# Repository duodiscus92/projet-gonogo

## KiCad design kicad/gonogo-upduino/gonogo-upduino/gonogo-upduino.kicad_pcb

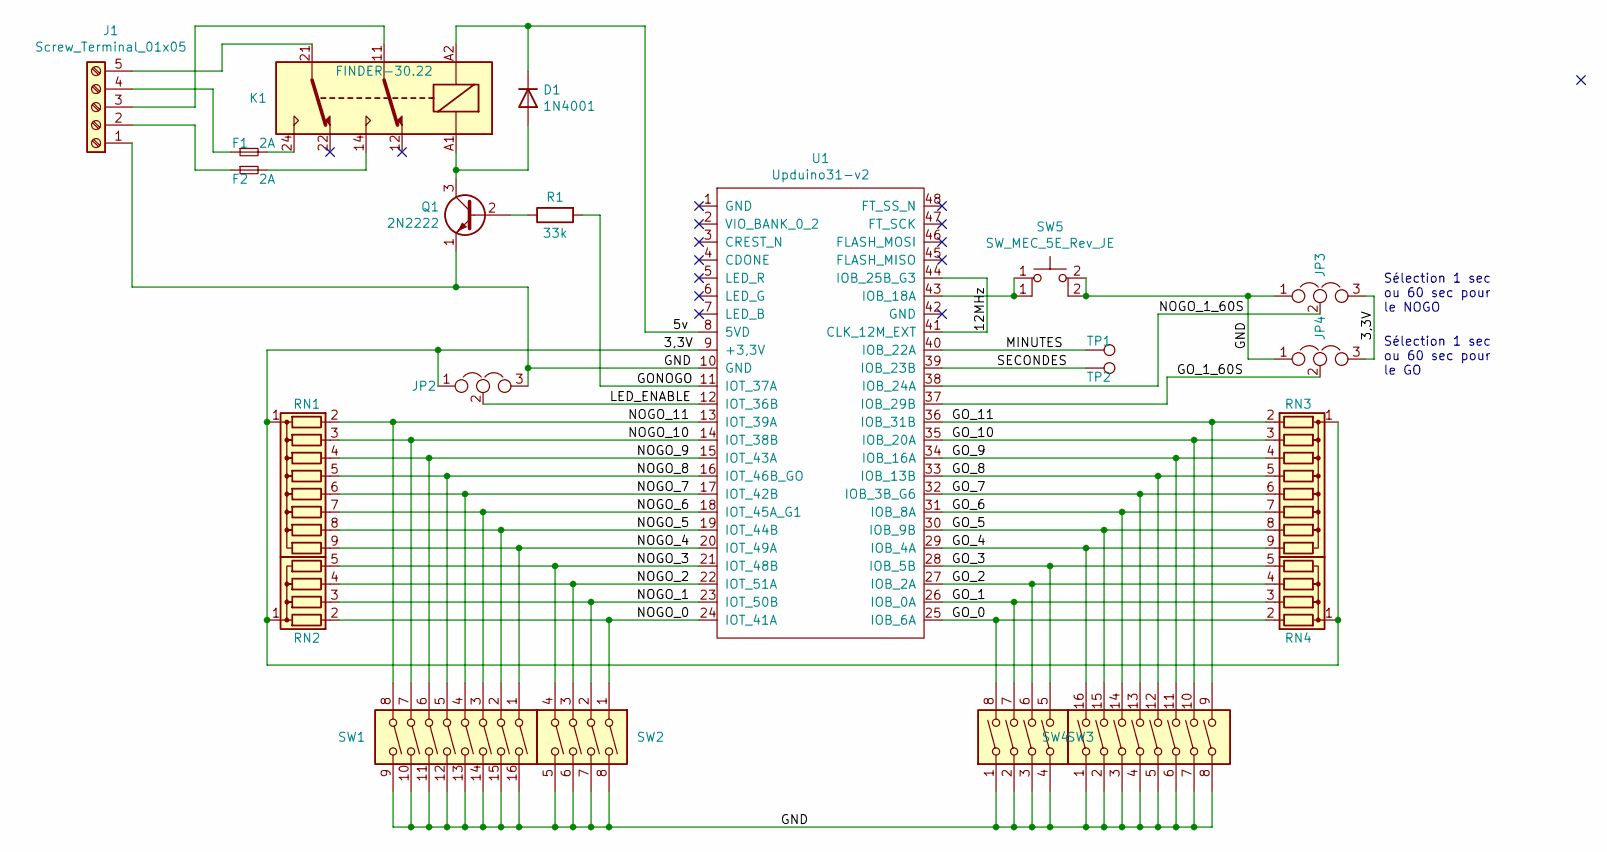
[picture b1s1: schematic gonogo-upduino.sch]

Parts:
D1: 1N4001; D_DO-41_SOD81_P10.16mm_Horizontal
F1, F2: 2A; Fuseholder_TR5_Littelfuse_No560_No460
J1: Screw_Terminal_01x05; TerminalBlock_bornier-5_P5.08mm
JP2, JP3, JP4: Jumper_NC_Dual; PinHeader_1x03_P2.54mm_Vertical
K1: FINDER-30.22; Relay_DPDT_Finder_30.22
Q1: 2N2222; TO-18-3
R1: 33k; R_Axial_DIN0207_L6.3mm_D2.5mm_P2.54mm_Vertical
RN1, RN3: R_Network08; R_Array_SIP9
RN2, RN4: R_Network04; R_Array_SIP5
SW1, SW4: SW_DIP_x08; DIP-16_W7.62mm_Socket
SW2, SW3: SW_DIP_x04; DIP-8_W7.62mm_Socket
SW5: SW_MEC_5E_Rev_JE; SW_PUSH_6mm
TP1, TP2: TestPoint; TestPoint_THTPad_3.0x3.0mm_Drill1.5mm
U1: Upduino31-v2; DIP-48_W17.78mm_LongPads

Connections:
/3,3V: JP2.1, JP3.3, JP4.3, RN1.1 (common), RN2.1 (common), RN3.1 (common), RN4.1 (common), U1.9 (+3,3V)
/5v: D1.1 (K), K1.A2, U1.8 (5VD)
/12MHz: U1.41 (CLK_12M_EXT), U1.44 (IOB_25B_G3)
/GND: J1.1, JP2.3, JP3.1, JP4.1, Q1.1 (E), SW1.9, SW1.10, SW1.11, SW1.12, SW1.13, SW1.14, SW1.15, SW1.16, SW2.5, SW2.6, SW2.7, SW2.8, SW3.1, SW3.2, SW3.3, SW3.4, SW4.1, SW4.2, SW4.3, SW4.4, SW4.5, SW4.6, SW4.7, SW4.8, SW5.2 (A), U1.10 (GND)
/GONOGO: R1.2, U1.11 (IOT_37A)
/GO_0: RN4.2 (R1), SW3.8, U1.25 (IOB_6A)
/GO_1: RN4.3 (R2), SW3.7, U1.26 (IOB_0A)
/GO_1_60S: JP4.2, U1.37 (IOB_29B)
/GO_2: RN4.4 (R3), SW3.6, U1.27 (IOB_2A)
/GO_3: RN4.5 (R4), SW3.5, U1.28 (IOB_5B)
/GO_4: RN3.9 (R8), SW4.16, U1.29 (IOB_4A)
/GO_5: RN3.8 (R7), SW4.15, U1.30 (IOB_9B)
/GO_6: RN3.7 (R6), SW4.14, U1.31 (IOB_8A)
/GO_7: RN3.6 (R5), SW4.13, U1.32 (IOB_3B_G6)
/GO_8: RN3.5 (R4), SW4.12, U1.33 (IOB_13B)
/GO_9: RN3.4 (R3), SW4.11, U1.34 (IOB_16A)
/GO_10: RN3.3 (R2), SW4.10, U1.35 (IOB_20A)
/GO_11: RN3.2 (R1), SW4.9, U1.36 (IOB_31B)
/LED_ENABLE: JP2.2, U1.12 (IOT_36B)
/MINUTES: TP1.1, U1.40 (IOB_22A)
/NOGO_0: RN2.2 (R1), SW2.1, U1.24 (IOT_41A)
/NOGO_1: RN2.3 (R2), SW2.2, U1.23 (IOT_50B)
/NOGO_1_60S: JP3.2, U1.38 (IOB_24A)
/NOGO_2: RN2.4 (R3), SW2.3, U1.22 (IOT_51A)
/NOGO_3: RN2.5 (R4), SW2.4, U1.21 (IOT_48B)
/NOGO_4: RN1.9 (R8), SW1.1, U1.20 (IOT_49A)
/NOGO_5: RN1.8 (R7), SW1.2, U1.19 (IOT_44B)
/NOGO_6: RN1.7 (R6), SW1.3, U1.18 (IOT_45A_G1)
/NOGO_7: RN1.6 (R5), SW1.4, U1.17 (IOT_42B)
/NOGO_8: RN1.5 (R4), SW1.5, U1.16 (IOT_46B_GO)
/NOGO_9: RN1.4 (R3), SW1.6, U1.15 (IOT_43A)
/NOGO_10: RN1.3 (R2), SW1.7, U1.14 (IOT_38B)
/NOGO_11: RN1.2 (R1), SW1.8, U1.13 (IOT_39A)
/SECONDES: TP2.1, U1.39 (IOB_23B)
unnamed: D1.2 (A), K1.A1, Q1.3 (C)
unnamed: F1.1, J1.4
unnamed: F1.2, K1.24
unnamed: F2.1, J1.2
unnamed: F2.2, K1.14
unnamed: J1.3, K1.11
unnamed: J1.5, K1.21
unnamed: Q1.2 (B), R1.1
unnamed: SW5.1, U1.43 (IOB_18A)

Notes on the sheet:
Sélection 1 sec ou 60 sec pour le NOGO
Sélection 1 sec ou 60 sec pour le GO

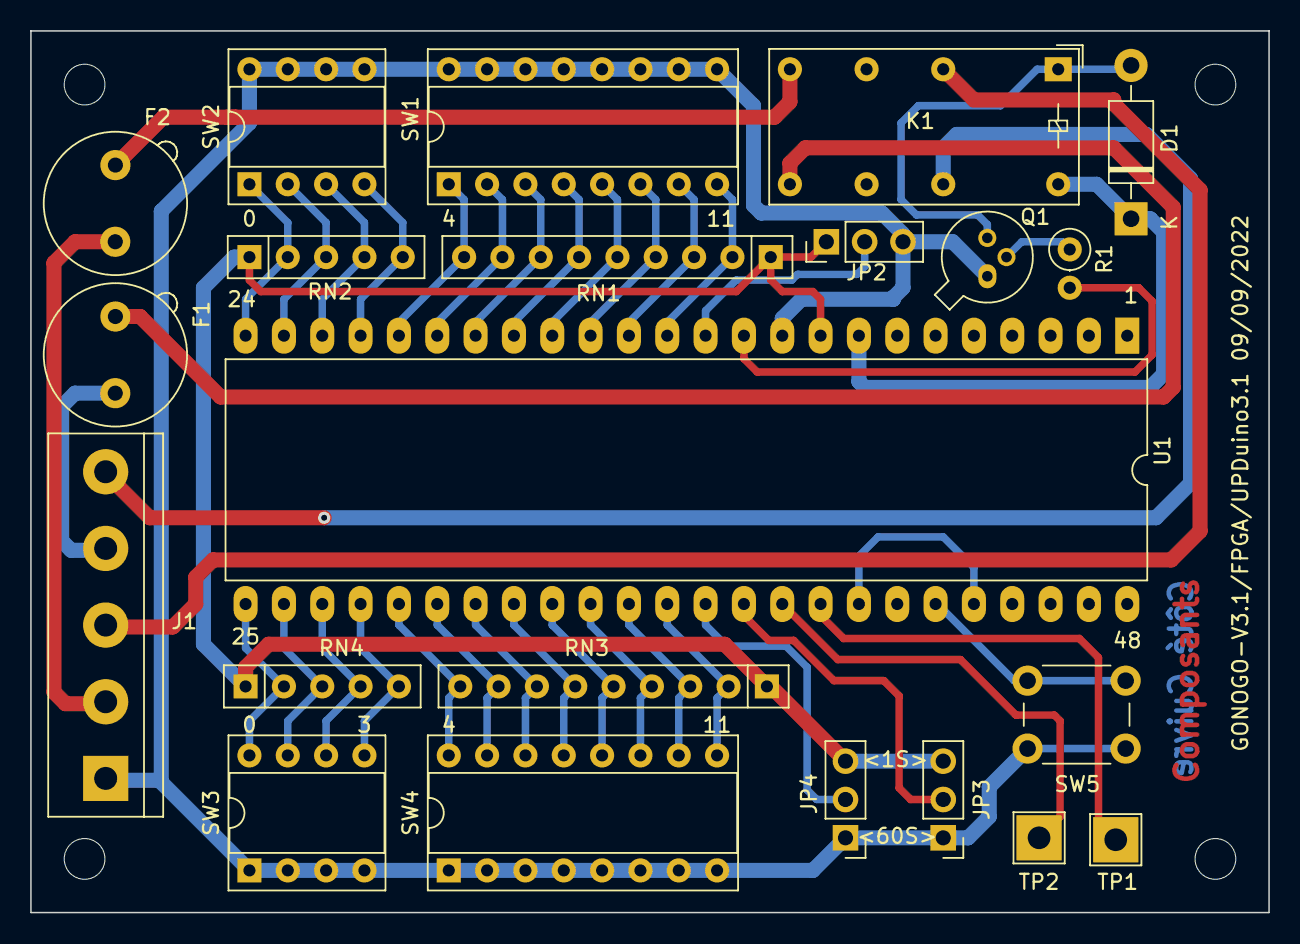
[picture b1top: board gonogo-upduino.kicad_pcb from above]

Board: 2 copper layers, 82.0 x 58.4 mm, 23 parts (0 on the bottom side), 43 nets.

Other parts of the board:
NOGO-0: MountingHole_2.7mm_M2.5_DIN965

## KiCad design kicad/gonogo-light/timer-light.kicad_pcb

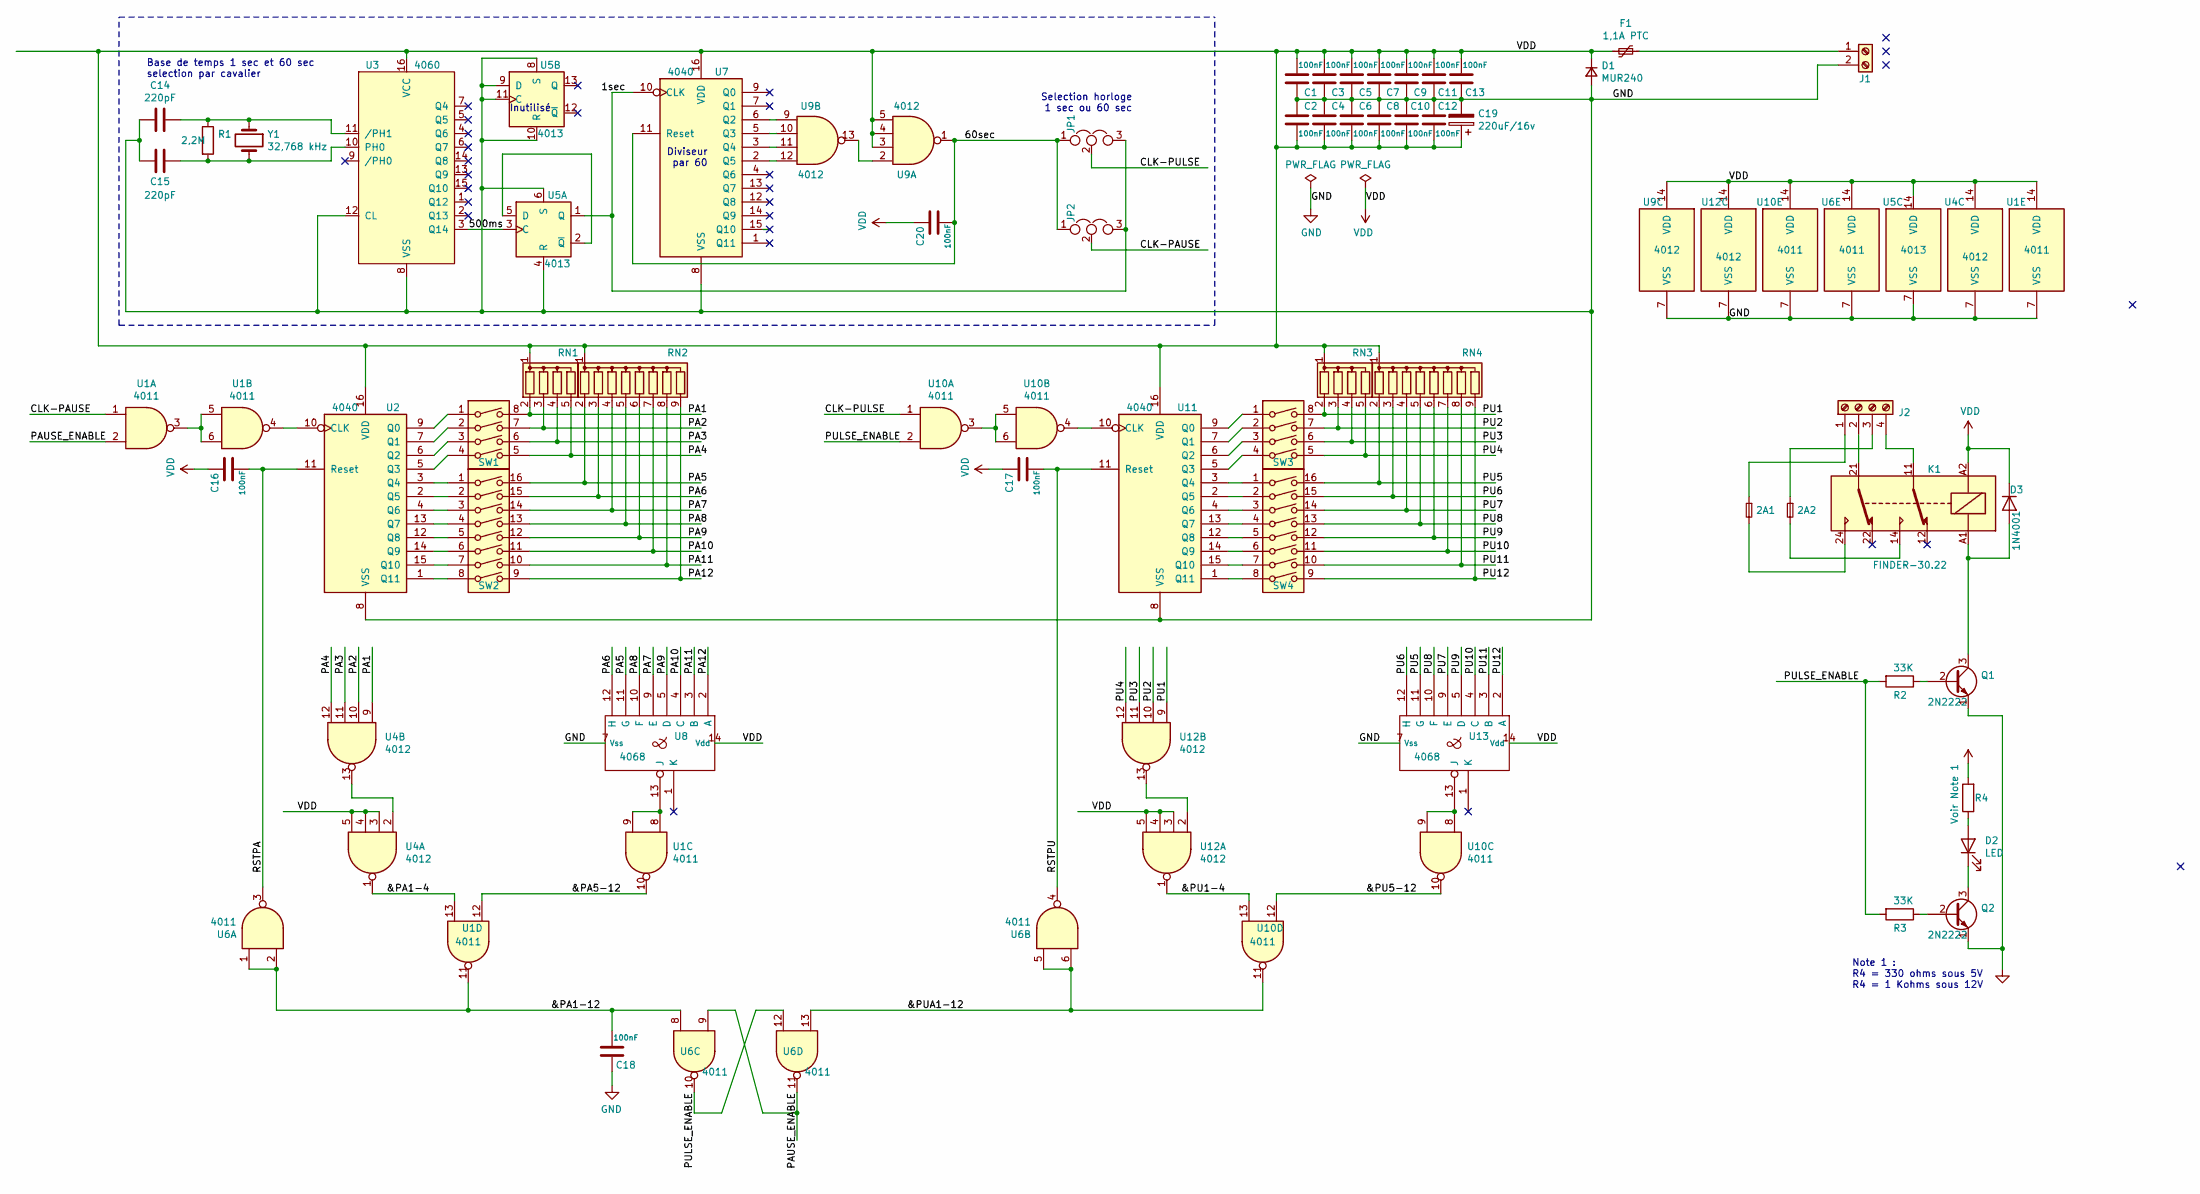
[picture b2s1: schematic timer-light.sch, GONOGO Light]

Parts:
2A1, 2A2: Fuse_Small; Fuseholder_TR5_Littelfuse_No560_No460
C1, C2, C3, C4, C5, C6, C7, C8, C9, C10, C11, C12, C13, C16, C17, C18, C20: 100nF; C_Rect_L7.2mm_W2.5mm_P5.00mm_FKS2_FKP2_MKS2_MKP2
C14, C15: 220pF; C_Rect_L7.2mm_W4.5mm_P5.00mm_FKS2_FKP2_MKS2_MKP2
C19: 220uF/16v; CP_Radial_D10.0mm_P5.00mm
D1: MUR240; D_DO-41_SOD81_P10.16mm_Horizontal
D2: LED; LED_D5.0mm
D3: 1N4001; D_DO-41_SOD81_P10.16mm_Horizontal
F1: 1,1A PTC; D_DO-41_SOD81_P10.16mm_Horizontal
J1: Screw_Terminal_01x02; TerminalBlock_bornier-2_P5.08mm
J2: Screw_Terminal_01x04; TerminalBlock_bornier-4_P5.08mm
JP1, JP2: Jumper_NC_Dual; PinHeader_1x03_P2.54mm_Vertical
K1: FINDER-30.22; Relay_DPDT_Finder_30.22
Q1, Q2: 2N2222; TO-18-3
R1: 2,2M; R_Axial_DIN0207_L6.3mm_D2.5mm_P10.16mm_Horizontal
R2, R3: 33K; R_Axial_DIN0207_L6.3mm_D2.5mm_P10.16mm_Horizontal
R4: Voir Note 1; R_Axial_DIN0207_L6.3mm_D2.5mm_P10.16mm_Horizontal
RN1, RN3: R_Network04; R_Array_SIP5
RN2, RN4: R_Network08; R_Array_SIP9
SW1, SW3: SW_DIP_x04; DIP-8_W7.62mm_Socket
SW2, SW4: SW_DIP_x08; DIP-16_W7.62mm_Socket
U1, U6, U10: 4011; DIP-14_W7.62mm_Socket
U2, U7, U11: 4040; DIP-16_W7.62mm_Socket
U3: 4060; DIP-16_W7.62mm_Socket
U4, U9, U12: 4012; DIP-14_W7.62mm_Socket
U5: 4013; DIP-14_W7.62mm_Socket
U8, U13: 4068; DIP-14_W7.62mm_Socket
Y1: 32,768 kHz; Crystal_C26-LF_D2.1mm_L6.5mm_Vertical

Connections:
/1sec: JP1.3, JP2.3, U5.1 (Q), U7.10 (CLK)
/60sec: C20.2, JP1.1, JP2.1, U7.11 (Reset), U9.1
/500ms: U3.3 (Q14), U5.3 (C)
/&PA1-4: U1.13, U4.1
/&PA1-12: C18.2, U1.11, U6.1, U6.2, U6.8
/&PA5-12: U1.10, U1.12
/&PU1-4: U10.13, U12.1
/&PU5-12: U10.10, U10.12
/&PUA1-12: U6.5, U6.6, U6.13, U10.11
/CLK-PAUSE: JP2.2, U1.1
/CLK-PULSE: JP1.2, U10.1
/PA1: RN1.2 (R1), SW1.8, U4.9
/PA2: RN1.3 (R2), SW1.7, U4.10
/PA3: RN1.4 (R3), SW1.6, U4.11
/PA4: RN1.5 (R4), SW1.5, U4.12
/PA5: RN2.2 (R1), SW2.16, U8.11 (G)
/PA6: RN2.3 (R2), SW2.15, U8.12 (H)
/PA7: RN2.4 (R3), SW2.14, U8.9 (E)
/PA8: RN2.5 (R4), SW2.13, U8.10 (F)
/PA9: RN2.6 (R5), SW2.12, U8.5 (D)
/PA10: RN2.7 (R6), SW2.11, U8.4 (C)
/PA11: RN2.8 (R7), SW2.10, U8.3 (B)
/PA12: RN2.9 (R8), SW2.9, U8.2 (A)
/PAUSE_ENABLE: U1.2, U6.9, U6.11
/PU1: RN3.2 (R1), SW3.8, U12.9
/PU2: RN3.3 (R2), SW3.7, U12.10
/PU3: RN3.4 (R3), SW3.6, U12.11
/PU4: RN3.5 (R4), SW3.5, U12.12
/PU5: RN4.2 (R1), SW4.16, U13.11 (G)
/PU6: RN4.3 (R2), SW4.15, U13.12 (H)
/PU7: RN4.4 (R3), SW4.14, U13.9 (E)
/PU8: RN4.5 (R4), SW4.13, U13.10 (F)
/PU9: RN4.6 (R5), SW4.12, U13.5 (D)
/PU10: RN4.7 (R6), SW4.11, U13.4 (C)
/PU11: RN4.8 (R7), SW4.10, U13.3 (B)
/PU12: RN4.9 (R8), SW4.9, U13.2 (A)
/PULSE_ENABLE: R2.2, R3.2, U6.10, U6.12, U10.2
/RSTPA: C16.2, U2.11 (Reset), U6.3
/RSTPU: C17.2, U6.4, U11.11 (Reset)
GND: C1.1, C2.1, C3.1, C4.1, C5.1, C6.1, C7.1, C8.1, C9.1, C10.1, C11.1, C12.1, C13.1, C14.2, C15.2, C18.1, C19.2, D1.2 (A), J1.2, Q1.1 (E), Q2.1 (E), U1.7 (VSS), U2.8 (VSS), U3.8 (VSS), U3.12 (CL), U4.7 (VSS), U5.4 (R), U5.6 (S), U5.7 (VSS), U5.8 (S), U5.9 (D), U5.10 (R), U5.11 (C), U6.7 (VSS), U7.8 (VSS), U8.7 (Vss), U9.7 (VSS), U10.7 (VSS), U11.8 (VSS), U12.7 (VSS), U13.7 (Vss)
unnamed: 2A1.1, J2.1
unnamed: 2A1.2, K1.24
unnamed: 2A2.1, J2.3
unnamed: 2A2.2, K1.14
unnamed: C14.1, R1.1, U3.11 (/PH1), Y1.1
unnamed: C15.1, R1.2, U3.10 (PH0), Y1.2
unnamed: D2.1 (K), Q2.3 (C)
unnamed: D2.2 (A), R4.1
unnamed: D3.2 (A), K1.A1, Q1.3 (C)
unnamed: F1.1, J1.1
unnamed: J2.2, K1.21
unnamed: J2.4, K1.11
unnamed: Q1.2 (B), R2.1
unnamed: Q2.2 (B), R3.1
unnamed: SW1.1, U2.9 (Q0)
unnamed: SW1.2, U2.7 (Q1)
unnamed: SW1.3, U2.6 (Q2)
unnamed: SW1.4, U2.5 (Q3)
unnamed: SW2.1, U2.3 (Q4)
unnamed: SW2.2, U2.2 (Q5)
unnamed: SW2.3, U2.4 (Q6)
unnamed: SW2.4, U2.13 (Q7)
unnamed: SW2.5, U2.12 (Q8)
unnamed: SW2.6, U2.14 (Q9)
unnamed: SW2.7, U2.15 (Q10)
unnamed: SW2.8, U2.1 (Q11)
unnamed: SW3.1, U11.9 (Q0)
unnamed: SW3.2, U11.7 (Q1)
unnamed: SW3.3, U11.6 (Q2)
unnamed: SW3.4, U11.5 (Q3)
unnamed: SW4.1, U11.3 (Q4)
unnamed: SW4.2, U11.2 (Q5)
unnamed: SW4.3, U11.4 (Q6)
unnamed: SW4.4, U11.13 (Q7)
unnamed: SW4.5, U11.12 (Q8)
unnamed: SW4.6, U11.14 (Q9)
unnamed: SW4.7, U11.15 (Q10)
unnamed: SW4.8, U11.1 (Q11)
unnamed: U1.3, U1.5, U1.6
unnamed: U1.4, U2.10 (CLK)
unnamed: U1.8, U1.9, U8.13 (J)
unnamed: U4.2, U4.13
unnamed: U5.2 (~Q), U5.5 (D)
unnamed: U7.2 (Q5), U9.12
unnamed: U7.3 (Q4), U9.11
unnamed: U7.5 (Q3), U9.10
unnamed: U7.6 (Q2), U9.9
unnamed: U9.2, U9.13
unnamed: U10.3, U10.5, U10.6
unnamed: U10.4, U11.10 (CLK)
unnamed: U10.8, U10.9, U13.13 (J)
unnamed: U12.2, U12.13
VDD: C1.2, C2.2, C3.2, C4.2, C5.2, C6.2, C7.2, C8.2, C9.2, C10.2, C11.2, C12.2, C13.2, C16.1, C17.1, C19.1, C20.1, D1.1 (K), D3.1 (K), F1.2, K1.A2, R4.2, RN1.1 (common), RN2.1 (common), RN3.1 (common), RN4.1 (common), U1.14 (VDD), U2.16 (VDD), U3.16 (VCC), U4.3, U4.4, U4.5, U4.14 (VDD), U5.14 (VDD), U6.14 (VDD), U7.16 (VDD), U8.14 (Vdd), U9.3, U9.4, U9.5, U9.14 (VDD), U10.14 (VDD), U11.16 (VDD), U12.3, U12.4, U12.5, U12.14 (VDD), U13.14 (Vdd)

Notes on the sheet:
Base de temps 1 sec et 60 sec selection par cavalier
Inutilisé
Diviseur par 60
Selection horloge 1 sec ou 60 sec
Note 1 : R4 = 330 ohms sous 5V R4 = 1 Kohms sous 12V

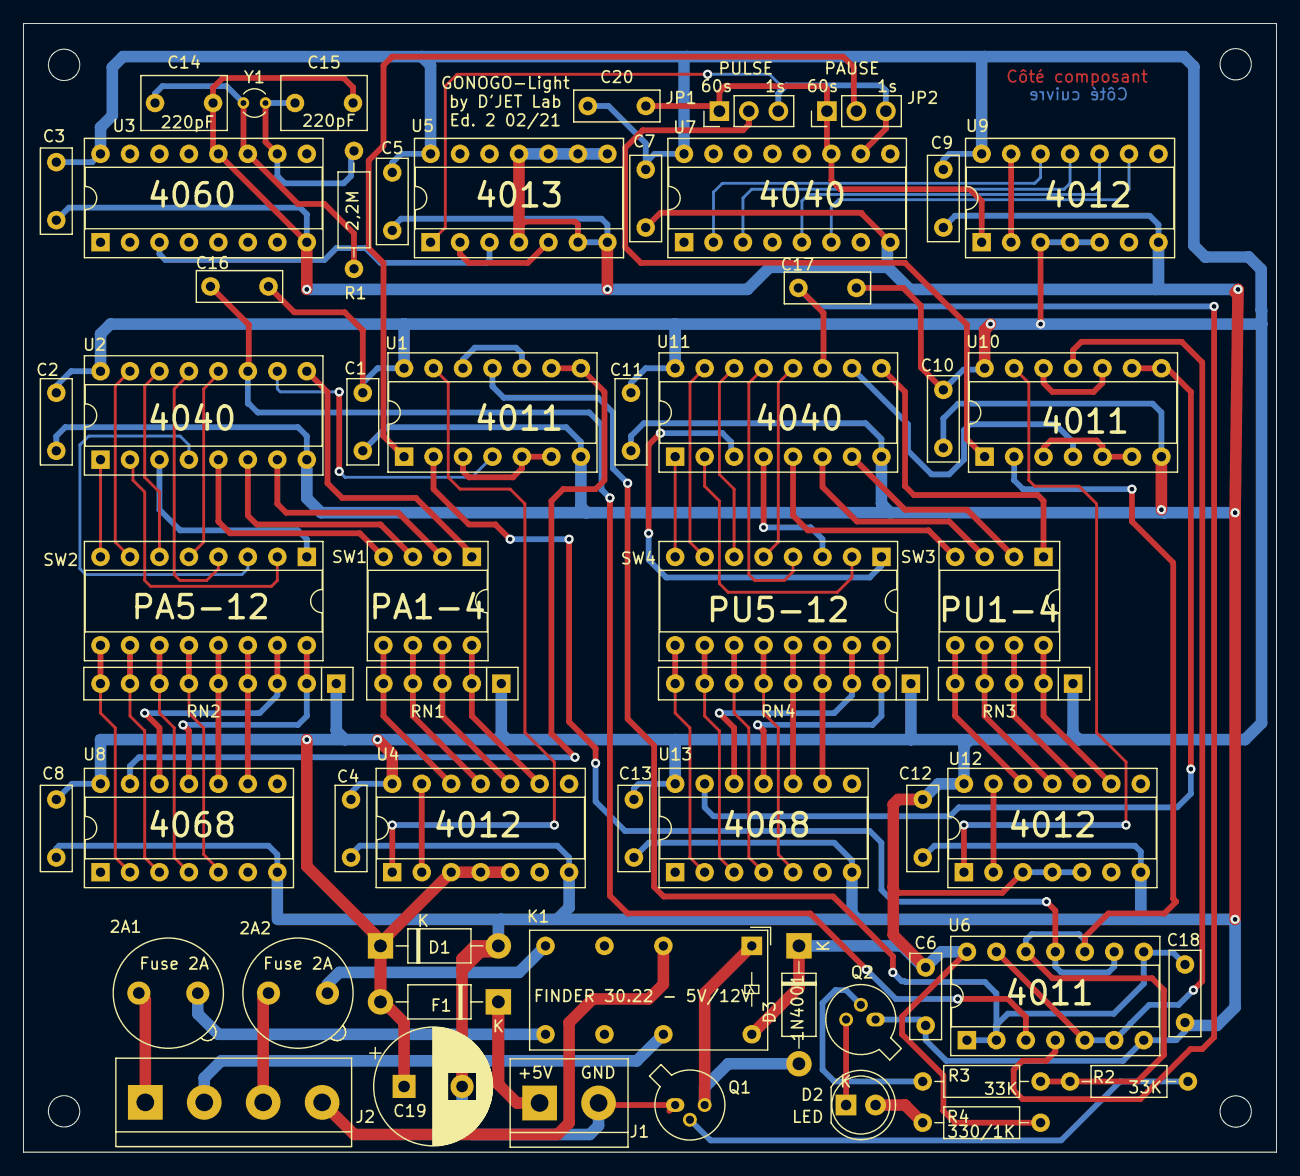
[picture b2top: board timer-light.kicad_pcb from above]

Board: 2 copper layers, 108.0 x 97.3 mm, 59 parts (0 on the bottom side), 93 nets.

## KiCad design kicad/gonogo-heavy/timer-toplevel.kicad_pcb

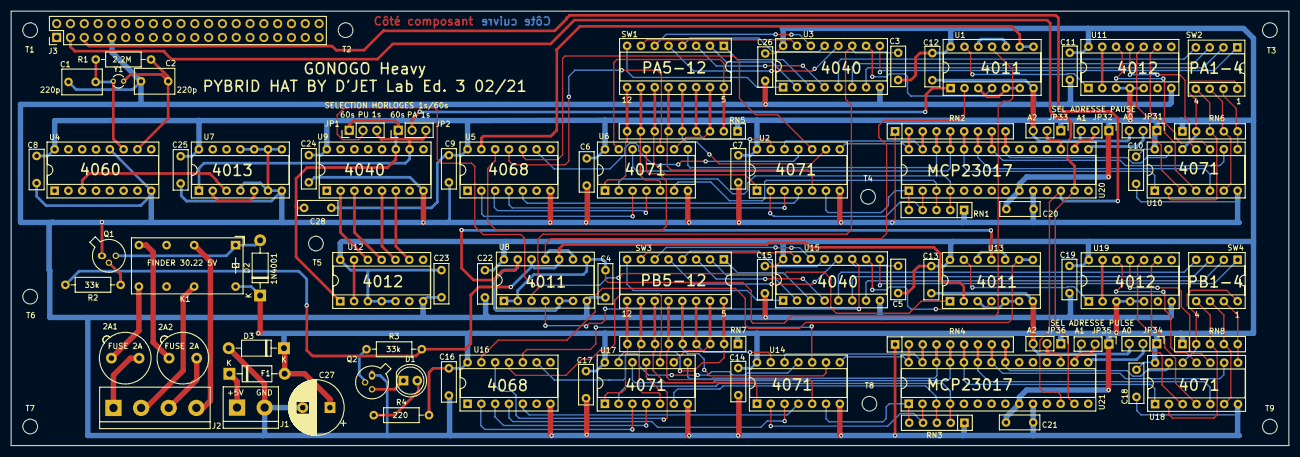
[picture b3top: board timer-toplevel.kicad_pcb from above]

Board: 2 copper layers, 234.9 x 79.9 mm, 95 parts (0 on the bottom side), 149 nets.

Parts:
2A1, 2A2: Fuse_Small; Fuseholder_TR5_Littelfuse_No560_No460
C1, C2: 220pF; C_Rect_L7.2mm_W4.5mm_P5.00mm_FKS2_FKP2_MKS2_MKP2
C3, C4, C5, C6, C7, C8, C9, C10, C11, C12, C13, C14, C15, C16, C17, C18, C19, C20, C21, C22, C23, C24, C25, C26, C28: 100nF; C_Rect_L7.2mm_W2.5mm_P5.00mm_FKS2_FKP2_MKS2_MKP2
C27: 220uF/16v; CP_Radial_D10.0mm_P5.00mm
D1: LED; LED_D5.0mm
D2: 1N4001; D_DO-41_SOD81_P10.16mm_Horizontal
D3: MUR240; D_DO-41_SOD81_P10.16mm_Horizontal
F1: 1,1A PTC; D_DO-41_SOD81_P10.16mm_Horizontal
J1: Screw_Terminal_01x02; TerminalBlock_bornier-2_P5.08mm
J2: Screw_Terminal_01x04; TerminalBlock_bornier-4_P5.08mm
J3: Raspberry_Pi_2_3; PinHeader_2x20_P2.54mm_Vertical
JP1, JP2, JP31, JP32, JP33, JP34, JP35, JP36: Jumper_NC_Dual; PinHeader_1x03_P2.54mm_Vertical
K1: FINDER-30.22; Relay_DPDT_Finder_30.22
Q1, Q2: 2N2222; TO-18-3
R1: 2,2M; R_Axial_DIN0207_L6.3mm_D2.5mm_P10.16mm_Horizontal
R2, R3: 33K; R_Axial_DIN0207_L6.3mm_D2.5mm_P10.16mm_Horizontal
R4: 10k; R_Axial_DIN0207_L6.3mm_D2.5mm_P10.16mm_Horizontal
RN1, RN3, RN6, RN8: R_Network04; R_Array_SIP5
RN2, RN4, RN5, RN7: R_Network08; R_Array_SIP9
SW1, SW3: SW_DIP_x08; DIP-16_W7.62mm_Socket
SW2, SW4: SW_DIP_x04; DIP-8_W7.62mm_Socket
T1, T2, T3, T4, T5, T6, T7, T8, T9: MountingHole_2.7mm_M2.5_DIN965
U1, U8, U13: 4011; DIP-14_W7.62mm_Socket
U2, U6, U10, U14, U17, U18: 4071; DIP-14_W7.62mm_Socket
U3, U9, U15: 4040; DIP-16_W7.62mm_Socket
U4: 4060; DIP-16_W7.62mm_Socket
U5, U16: 4068; DIP-14_W7.62mm_Socket
U7: 4013; DIP-14_W7.62mm_Socket
U11, U12, U19: 4012; DIP-14_W7.62mm_Socket
U20, U21: MCP23017_SP; DIP-28_W7.62mm_Socket
Y1: 32,768 kHz; Crystal_C26-LF_D2.1mm_L6.5mm_Vertical

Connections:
/Pulse-pause timer 1 de 2/1sec: JP1.3, JP2.3, U7.1, U9.10
/Pulse-pause timer 1 de 2/60sec: C28.2, JP1.1, JP2.1, U9.11, U12.1
/Pulse-pause timer 1 de 2/500ms: U4.3, U7.3
/Pulse-pause timer 1 de 2/&PPA1-4: U1.13, U11.1
/Pulse-pause timer 1 de 2/&PPA5-12: U1.10, U1.12
/Pulse-pause timer 1 de 2/&PPU1-4: U13.13, U19.1
/Pulse-pause timer 1 de 2/&PPU5-12: U13.10, U13.12
/Pulse-pause timer 1 de 2/CLK-PAUSE: JP2.2, U1.1
/Pulse-pause timer 1 de 2/CLK-PULSE: JP1.2, U13.1
/Pulse-pause timer 1 de 2/P1: RN2.9, U10.13, U20.21
/Pulse-pause timer 1 de 2/P2: RN2.8, U10.9, U20.22
/Pulse-pause timer 1 de 2/P3: RN2.7, U10.5, U20.23
/Pulse-pause timer 1 de 2/P4: RN2.6, U10.1, U20.24
/Pulse-pause timer 1 de 2/P5: RN2.5, U6.12, U20.25
/Pulse-pause timer 1 de 2/P6: RN2.4, U6.8, U20.26
/Pulse-pause timer 1 de 2/P7: RN2.3, U2.12, U20.27
/Pulse-pause timer 1 de 2/P8: RN2.2, U2.8, U20.28
/Pulse-pause timer 1 de 2/P9: RN1.5, U2.6, U20.1
/Pulse-pause timer 1 de 2/P10: RN1.4, U2.2, U20.2
/Pulse-pause timer 1 de 2/P11: RN1.3, U6.6, U20.3
/Pulse-pause timer 1 de 2/P12: RN1.2, U6.2, U20.4
/Pulse-pause timer 1 de 2/PA1: RN6.2, SW2.8, U10.12
/Pulse-pause timer 1 de 2/PA2: RN6.5, SW2.7, U10.8
/Pulse-pause timer 1 de 2/PA3: RN6.4, SW2.6, U10.6
/Pulse-pause timer 1 de 2/PA4: RN6.3, SW2.5, U10.2
/Pulse-pause timer 1 de 2/PA5: RN5.2, SW1.16, U6.13
/Pulse-pause timer 1 de 2/PA6: RN5.3, SW1.15, U6.9
/Pulse-pause timer 1 de 2/PA7: RN5.4, SW1.14, U2.13
/Pulse-pause timer 1 de 2/PA8: RN5.5, SW1.13, U2.9
/Pulse-pause timer 1 de 2/PA9: RN5.6, SW1.12, U2.5
/Pulse-pause timer 1 de 2/PA10: RN5.7, SW1.11, U2.1
/Pulse-pause timer 1 de 2/PA11: RN5.8, SW1.10, U6.5
/Pulse-pause timer 1 de 2/PA12: RN5.9, SW1.9, U6.1
/Pulse-pause timer 1 de 2/PAUSE_ENABLE: U1.2, U8.9, U8.11
/Pulse-pause timer 1 de 2/PPA1: U10.11, U11.12
/Pulse-pause timer 1 de 2/PPA2: U10.10, U11.11
/Pulse-pause timer 1 de 2/PPA3: U10.4, U11.9
/Pulse-pause timer 1 de 2/PPA4: U10.3, U11.10
/Pulse-pause timer 1 de 2/PPA5: U5.12, U6.11
/Pulse-pause timer 1 de 2/PPA6: U5.11, U6.10
/Pulse-pause timer 1 de 2/PPA7: U2.11, U5.9
/Pulse-pause timer 1 de 2/PPA8: U2.10, U5.10
/Pulse-pause timer 1 de 2/PPA9: U2.4, U5.5
/Pulse-pause timer 1 de 2/PPA10: U2.3, U5.4
/Pulse-pause timer 1 de 2/PPA11: U5.3, U6.4
/Pulse-pause timer 1 de 2/PPA12: U5.2, U6.3
/Pulse-pause timer 1 de 2/PPU1: U18.11, U19.12
/Pulse-pause timer 1 de 2/PPU2: U18.10, U19.11
/Pulse-pause timer 1 de 2/PPU3: U18.4, U19.9
/Pulse-pause timer 1 de 2/PPU4: U18.3, U19.10
/Pulse-pause timer 1 de 2/PPU5: U16.12, U17.11
/Pulse-pause timer 1 de 2/PPU6: U16.11, U17.10
/Pulse-pause timer 1 de 2/PPU7: U14.11, U16.9
/Pulse-pause timer 1 de 2/PPU8: U14.10, U16.10
/Pulse-pause timer 1 de 2/PPU9: U14.4, U16.5
/Pulse-pause timer 1 de 2/PPU10: U14.3, U16.4
/Pulse-pause timer 1 de 2/PPU11: U16.3, U17.4
/Pulse-pause timer 1 de 2/PPU12: U16.2, U17.3
/Pulse-pause timer 1 de 2/PU1: RN8.2, SW4.8, U18.12
/Pulse-pause timer 1 de 2/PU2: RN8.5, SW4.7, U18.8
/Pulse-pause timer 1 de 2/PU3: RN8.4, SW4.6, U18.6
/Pulse-pause timer 1 de 2/PU4: RN8.3, SW4.5, U18.2
/Pulse-pause timer 1 de 2/PU5: RN7.2, SW3.16, U17.13
/Pulse-pause timer 1 de 2/PU6: RN7.3, SW3.15, U17.9
/Pulse-pause timer 1 de 2/PU7: RN7.4, SW3.14, U14.13
/Pulse-pause timer 1 de 2/PU8: RN7.5, SW3.13, U14.9
/Pulse-pause timer 1 de 2/PU9: RN7.6, SW3.12, U14.5
/Pulse-pause timer 1 de 2/PU10: RN7.7, SW3.11, U14.1
/Pulse-pause timer 1 de 2/PU11: RN7.8, SW3.10, U17.5
/Pulse-pause timer 1 de 2/PU12: RN7.9, SW3.9, U17.1
/Pulse-pause timer 1 de 2/PULSE_ENABLE: R2.2, R3.2, U8.10, U8.12, U13.2
/Pulse-pause timer 1 de 2/RSTPA: C3.2, U3.11, U8.3
/Pulse-pause timer 1 de 2/RSTPU: C5.2, U8.4, U15.11
/Pulse-pause timer 1 de 2/U1: RN4.9, U18.13, U21.21
/Pulse-pause timer 1 de 2/U2: RN4.8, U18.9, U21.22
/Pulse-pause timer 1 de 2/U3: RN4.7, U18.5, U21.23
/Pulse-pause timer 1 de 2/U4: RN4.6, U18.1, U21.24
/Pulse-pause timer 1 de 2/U5: RN4.5, U17.12, U21.25
/Pulse-pause timer 1 de 2/U6: RN4.4, U17.8, U21.26
/Pulse-pause timer 1 de 2/U7: RN4.3, U14.12, U21.27
/Pulse-pause timer 1 de 2/U8: RN4.2, U14.8, U21.28
/Pulse-pause timer 1 de 2/U9: RN3.5, U14.6, U21.1
/Pulse-pause timer 1 de 2/U10: RN3.4, U14.2, U21.2
/Pulse-pause timer 1 de 2/U11: RN3.3, U17.6, U21.3
/Pulse-pause timer 1 de 2/U12: RN3.2, U17.2, U21.4
/Pulse-pause timer 1 de 2/~&PPA1-12: C4.2, U1.11, U8.1, U8.2, U8.8
/Pulse-pause timer 1 de 2/~&PUA1-12: U8.5, U8.6, U8.13, U13.11
/Pulse-pause timer 2 de 2/SCK: J3.5, U20.12, U21.12
/Pulse-pause timer 2 de 2/SDA: J3.3, U20.13, U21.13
GND: C1.2, C2.2, C4.1, C6.1, C7.1, C8.1, C9.1, C10.1, C11.1, C12.1, C13.1, C14.1, C15.1, C16.1, C17.1, C18.1, C19.1, C20.1, C21.1, C22.1, C23.2, C24.2, C25.1, C26.1, C27.2, D3.2, J1.2, J3.9, JP31.3, JP32.3, JP33.3, JP34.3, JP35.3, JP36.3, Q1.1, Q2.1, RN1.1, RN2.1, RN3.1, RN4.1, U1.7, U2.7, U3.8, U4.8, U4.12, U5.7, U6.7, U7.4, U7.6, U7.7, U7.8, U7.9, U7.10, U7.11, U8.7, U9.8, U10.7, U11.7, U12.7, U13.7, U14.7, U15.8, U16.7, U17.7, U18.7, U19.7, U20.10, U21.10
unnamed: 2A1.1, J2.1
unnamed: 2A1.2, K1.24
unnamed: 2A2.1, J2.3
unnamed: 2A2.2, K1.14
unnamed: C1.1, R1.1, U4.11, Y1.1
unnamed: C2.1, R1.2, U4.10, Y1.2
unnamed: D1.1, Q2.3
unnamed: D1.2, R4.1
unnamed: D2.2, K1.A1, Q1.3
unnamed: F1.1, J1.1
unnamed: J2.2, K1.21
unnamed: J2.4, K1.11
unnamed: JP31.2, U20.15
unnamed: JP32.2, U20.16
unnamed: JP33.2, U20.17
unnamed: JP34.2, U21.15
unnamed: JP35.2, U21.16
unnamed: JP36.2, U21.17
unnamed: Q1.2, R2.1
unnamed: Q2.2, R3.1
unnamed: SW1.1, U3.3
unnamed: SW1.2, U3.2
unnamed: SW1.3, U3.4
unnamed: SW1.4, U3.13
unnamed: SW1.5, U3.12
unnamed: SW1.6, U3.14
unnamed: SW1.7, U3.15
unnamed: SW1.8, U3.1
unnamed: SW2.1, U3.9
unnamed: SW2.2, U3.7
unnamed: SW2.3, U3.6
unnamed: SW2.4, U3.5
unnamed: SW3.1, U15.3
unnamed: SW3.2, U15.2
unnamed: SW3.3, U15.4
unnamed: SW3.4, U15.13
unnamed: SW3.5, U15.12
unnamed: SW3.6, U15.14
unnamed: SW3.7, U15.15
unnamed: SW3.8, U15.1
unnamed: SW4.1, U15.9
unnamed: SW4.2, U15.7
unnamed: SW4.3, U15.6
unnamed: SW4.4, U15.5
unnamed: U1.3, U1.5, U1.6
unnamed: U1.4, U3.10
unnamed: U1.8, U1.9, U5.13
unnamed: U7.2, U7.5
unnamed: U11.2, U11.13
unnamed: U9.6, U12.9
unnamed: U9.5, U12.10
unnamed: U9.3, U12.11
unnamed: U9.2, U12.12
unnamed: U12.2, U12.13
unnamed: U13.3, U13.5, U13.6
unnamed: U13.4, U15.10
unnamed: U13.8, U13.9, U16.13
unnamed: U19.2, U19.13
VDD: C3.1, C5.1, C6.2, C7.2, C8.2, C9.2, C10.2, C11.2, C12.2, C13.2, C14.2, C15.2, C16.2, C17.2, C18.2, C19.2, C20.2, C21.2, C22.2, C23.1, C24.1, C25.2, C26.2, C27.1, C28.1, D2.1, D3.1, F1.2, JP31.1, JP32.1, JP33.1, JP34.1, JP35.1, JP36.1, K1.A2, R4.2, RN5.1, RN6.1, RN7.1, RN8.1, U1.14, U2.14, U3.16, U4.16, U5.14, U6.14, U7.14, U8.14, U9.16, U10.14, U11.3, U11.4, U11.5, U11.14, U12.3, U12.4, U12.5, U12.14, U13.14, U14.14, U15.16, U16.14, U17.14, U18.14, U19.3, U19.4, U19.5, U19.14, U20.9, U21.9

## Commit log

2021-02-05 correction du readme
2021-02-07 ajout des fichiers source du programme gonogo-switch
2021-02-07 mise à jour du readme
2021-02-11 Correction d'une erreur dans le schéma et le pcb
2021-02-11 décalage des condensateurs 100nF dans pcb
2021-02-23 correction des erreurs et ajout de capas de reset sur poweron
2021-02-25 ajout du code source langage C mcp23017
2022-09-14 ajout du projet gonogo upduino
2022-09-14 ajout fichiers du projet gonogo upduino et publications
